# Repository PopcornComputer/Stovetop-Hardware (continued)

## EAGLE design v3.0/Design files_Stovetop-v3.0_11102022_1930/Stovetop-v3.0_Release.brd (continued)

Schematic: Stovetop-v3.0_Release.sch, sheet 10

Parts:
C5, C8, C12: 10uF; 0603-CAP
C9, C11, C13, C14: 22uF; 0805
C15, C16: 1uF; 0603-CAP
C43, C44, C45, C46: 220pF; 0603-CAP
C53, C54: 0.1uF; 0402-CAP
R4: 19.1K; R0402
R5, R10, R11, R13, R24, R30, R31, R32, R33, R34: 10K; R0402
R7: 28K; R0402
R23: 1M; R0402
TP2, TP4, TP5, TP6, TP7, TP8, TP9, TP10, TP11, TP12, TP13: TEST_POINT; TP-1MMX1MM
U8: TPS65988
U9: W25X05CLSNIG

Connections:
ADCIN1: R4.1, R5.2, U8.6 (ADCIN1)
ADCIN2: R7.1, R10.2, U8.10 (ADCIN2)
ANT_SELECT: TP12.0, U8.49 (GPIO17(PEXT2))
AUDIO_EN: TP11.0, U8.48 (GPIO16(PEXT1))
DRAIN1: U8.8 (DRAIN1), U8.15 (DRAIN1_1), U8.19 (DRAIN1_2), U8.58 (DRAIN1_3)
DRAIN2: U8.7 (DRAIN2), U8.52 (DRAIN2_1), U8.56 (DRAIN2_2), U8.57 (DRAIN2_3)
FAULT1: U8.22 (I2C3_SDA(GPIO6)); also elsewhere on the board
FAULT2: U8.23 (I2C3_IRQ(GPIO7)); also elsewhere on the board
GND: C5.1, C8.1, C9.1, C11.1, C12.1, C13.1, C14.1, C15.2, C16.2, C43.1, C44.1, C45.1, C46.1, C53.1, C54.1, R5.1, R10.1, R23.1, R24.1, U8.20 (GND), U8.51 (GND1), U8.59 (GND2), U9.4 (GND); also elsewhere on the board
HRESET: C54.2, R24.2, U8.44 (HRESET); also elsewhere on the board
I2C1_IRQZ: R34.1, U8.29 (I2C1_IRQ); also elsewhere on the board
I2C1_SCL: U8.27 (I2C1_SCL); also elsewhere on the board
I2C1_SDA: U8.28 (I2C1_SDA); also elsewhere on the board
I2C2_IRQZ: U8.34 (I2C2_IRQ)
I2C2_SCL: R11.1, U8.32 (I2C2_SCL)
I2C2_SDA: R13.1, U8.33 (I2C2_SDA)
LDO_1V8: C8.2, U8.35 (LDO_1V8)
LDO_3V3: C5.2, C53.2, R4.2, R7.2, R11.2, R13.2, R30.2, R31.2, R32.2, R33.2, R34.2, U8.9 (LDO_3V3), U9.8 (VCC); also elsewhere on the board
unnamed: R23.2, TP2.0, U8.17 (GPIO1)
unnamed: R30.1, U9.3 (/WP)
unnamed: R33.1, U9.7 (/HOLD)
PD0-CC1: C46.2, U8.24 (C1_CC1); also elsewhere on the board
PD0-CC2: C45.2, U8.26 (C1_CC2); also elsewhere on the board
PD1-CC1: C44.2, U8.45 (C2_CC1); also elsewhere on the board
PD1-CC2: C43.2, U8.47 (C2_CC2); also elsewhere on the board
PORT0-D+: U8.50 (C1_USB_P(GPIO18)); also elsewhere on the board
PORT0-D-: U8.53 (C1_USB_N(GPIO19)); also elsewhere on the board
PORT0_VBUS: C15.1, U8.13 (VBUS1), U8.14 (VBUS1_1); also elsewhere on the board
PORT1-D+: U8.54 (C2_USB_P(GPIO20)); also elsewhere on the board
PORT1-D-: U8.55 (C2_USB_N(GPIO21)); also elsewhere on the board
PORT1_VBUS: C16.1, U8.3 (VBUS2_1), U8.4 (VBUS2); also elsewhere on the board
SPI_CLK: U8.38 (SPI_CLK(GPIO10)), U9.6 (CLK)
SPI_CS: R32.1, U8.39 (SPI_SS(GPIO11)), U9.1 (/CS)
SPI_MISO: R31.1, U8.36 (SPI_MISO(GPIO8)), U9.2 (DO(IO1))
SPI_MOSI: U8.37 (SPI_MOSI(GPIO9)), U9.5 (DI(IO0))
USB_SWITCH_OC: TP7.0, U8.21 (I2C3_SCL(GPIO5))
VCC3V3: C12.2, U8.5 (VIN_3V3); also elsewhere on the board
VCC5V: C9.2, C11.2, U8.25 (PP1_CABLE), U8.46 (PP2_CABLE); also elsewhere on the board
VCC_IN: C13.2, C14.2, U8.1 (PP_HV2_1), U8.2 (PP_HV2), U8.11 (PP_HV1_1), U8.12 (PP_HV1); also elsewhere on the board
XIO-P1: TP4.0, U8.18 (GPIO2)
XIO-P2: TP5.0, U8.30 (HPD1(GPIO3))
XIO-P3: TP6.0, U8.31 (HPD2(GPIO4))
XIO-P4: TP13.0, U8.40 (GPIO12)
XIO-P5: TP8.0, U8.41 (GPIO13)
XIO-P6: TP9.0, U8.42 (GPIO14(PWM))
XIO-P7: TP10.0, U8.43 (GPIO15(PWM))

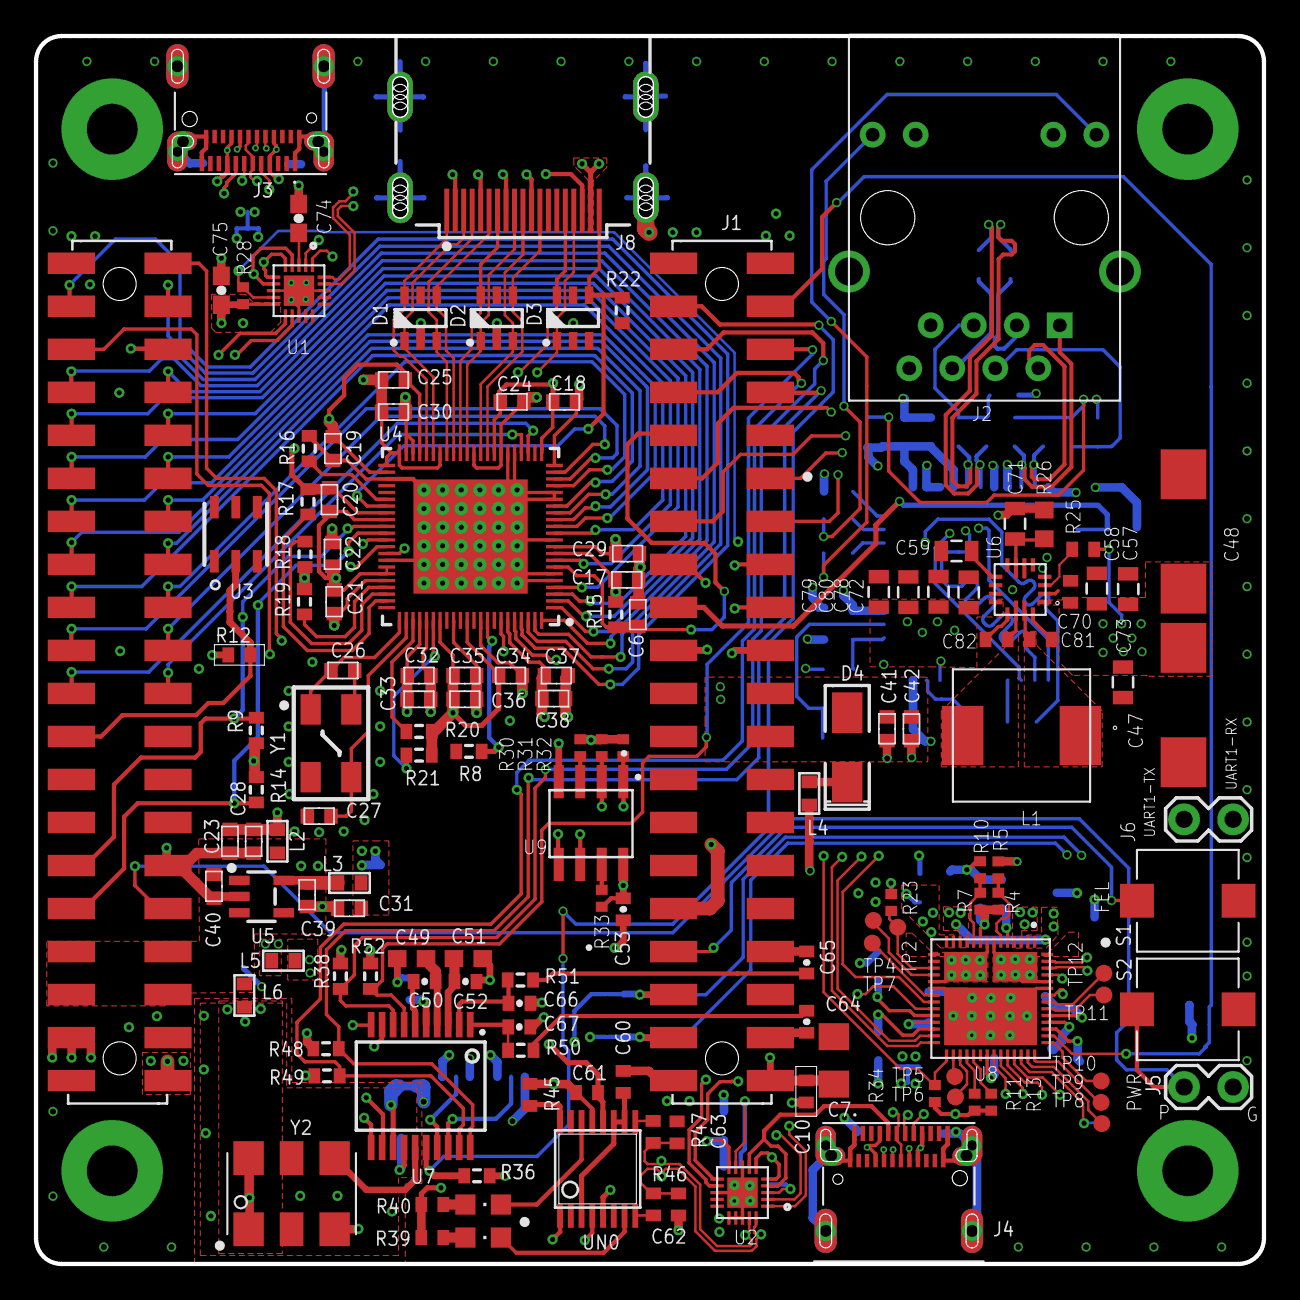
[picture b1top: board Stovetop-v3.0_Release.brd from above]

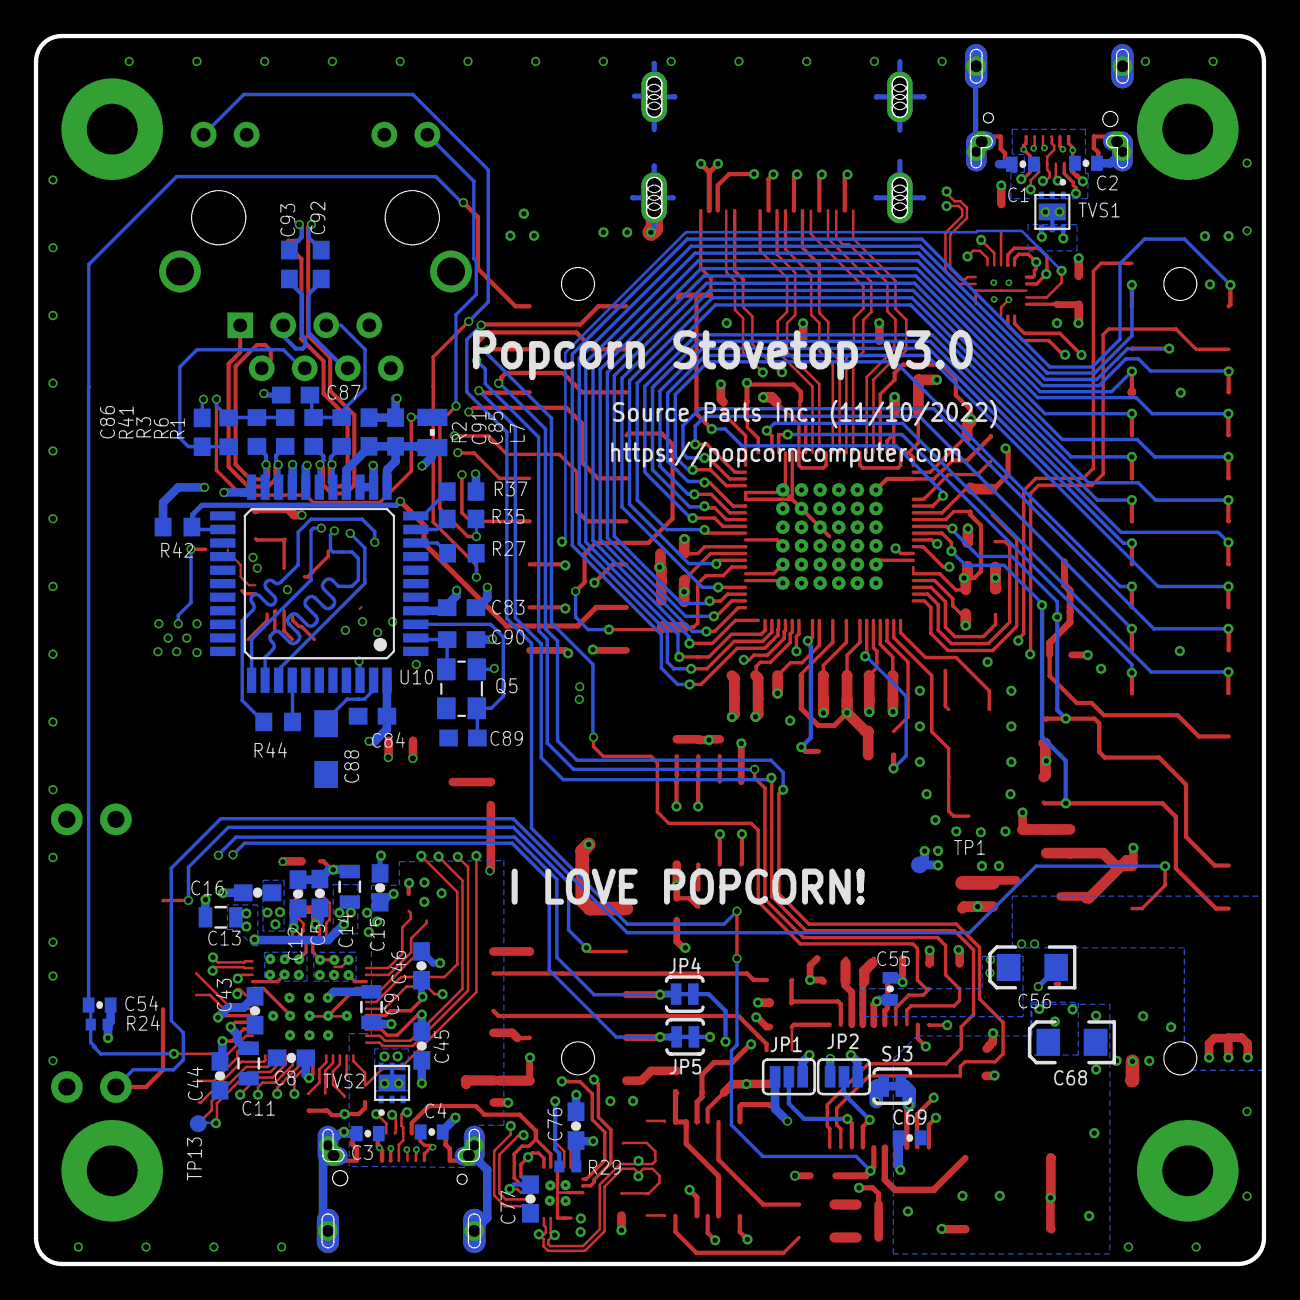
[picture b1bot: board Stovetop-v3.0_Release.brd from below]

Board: 6 copper layers, 72.5 x 72.5 mm, 200 parts (59 on the bottom side), 171 nets.

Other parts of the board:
DRILEGEND: DRILEGEND

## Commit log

2021-11-09 add v1.0
2022-09-30 ignore DS_Store
2022-10-21 add license
2022-10-21 add v3.0
2022-10-21 add social media links and license to README.md
2022-10-29 add documentation repo link and store link
2022-10-29 change to http secure link
